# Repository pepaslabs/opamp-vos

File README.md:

# opamp-vos

A board to measure the Vos (input offset voltage) of op amps.

# Latest release: v2.1

* Gerbers: [gerbers.zip](kicad/releases/v2.1/gerbers.zip)
* Schematic: [pdf](kicad/releases/v2.1/opamp-vos.pdf).

# License

This board design is [Open-Source Hardware](http://www.oshwa.org/definition/).  It is licensed under the [MIT License](http://opensource.org/licenses/MIT).  It was designed by Jason Pepas.

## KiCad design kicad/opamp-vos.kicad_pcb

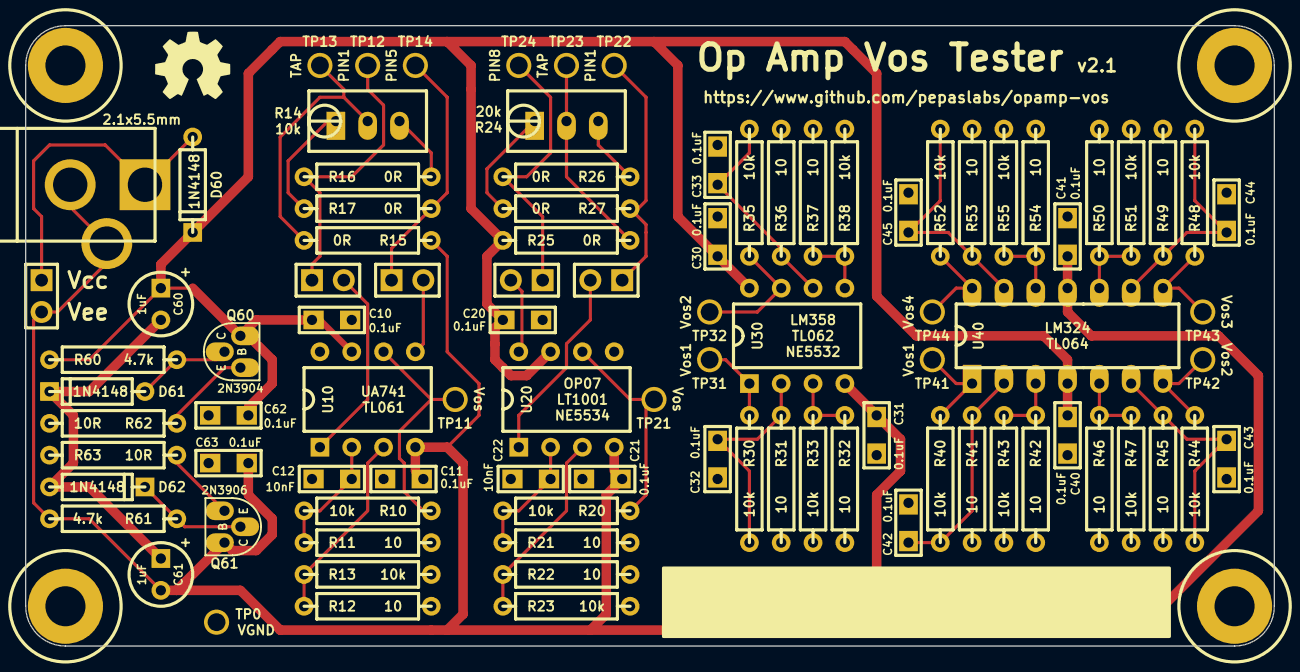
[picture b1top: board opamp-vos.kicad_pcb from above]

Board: 2 copper layers, 99.7 x 49.5 mm, 98 parts (0 on the bottom side), 47 nets.

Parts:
C10, C11, C20, C21, C30, C31, C32, C33, C40, C41, C42, C43, C44, C45, C62, C63: 0.1uF; CERCAP_15_059B_0805
C12, C22: 10nF; CERCAP_15_059B_0805
C60, C61: 1uF; ELCAP_10_20_V_059A
CON60: BARREL_JACK; BARREL_JACK_21x55
D60, D61, D62: 1N4148; DIODE_SS_059A_03_PL
H***: Val**; hole_M3
H***#2, H***#3, H***#4: Val**; hole_M3
JP10, JP11, JP20, JP21: JUMPER; SIL-2
P60: CONN_2X1; SIL-2
Q60: 2N3904; TO-92_Q_EBC_059Bo_PL
Q61: 2N3906; TO-92_Q_EBC_059Bo_PL
R10, R13, R20, R23, R30, R33, R35, R38, R40, R43, R44, R47, R48, R51, R52, R55: 10k; R_AXIAL_0W25_059A_PL
R11, R12, R21, R22, R31, R32, R36, R37, R41, R42, R45, R46, R49, R50, R53, R54: 10; R_AXIAL_0W25_059A_PL
R14: 10k; 3296W_PL
R15, R16, R17, R25, R26, R27: 0R; R_AXIAL_0W25_059A_PL
R24: 20k; 3296W_PL
R60, R61: 4.7k; R_AXIAL_0W25_059A_PL
R62, R63: 10R; R_AXIAL_0W25_059A_PL
TP0, TP11, TP12, TP13, TP14, TP21, TP22, TP23, TP24, TP31, TP32, TP41, TP42, TP43, TP44: TEST
U10: UA741; DIP8_059A_PL
U20: OP07; DIP8_059A_PL
U30: LM358; DIP8_059A_PL
U40: LM324; DIP14_PL

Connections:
unnamed: R42.1, R43.1, U40.3
unnamed: C42.1, R40.2, R41.1, U40.2
unnamed: C43.1, R44.2, R45.1, U40.6
unnamed: R46.1, R47.1, U40.5
unnamed: R24.2, R25.2, TP23.1
unnamed: JP21.1, R26.2, TP24.1
unnamed: R24.3, R26.1
unnamed: JP10.2, U10.1
unnamed: JP11.2, U10.5
unnamed: R14.3, R16.2
unnamed: JP20.2, U20.1
unnamed: JP21.2, U20.8
unnamed: R54.1, R55.1, U40.12
unnamed: R14.1, R17.1
unnamed: JP20.1, R27.1, TP22.1
unnamed: R24.1, R27.2
unnamed: C44.1, R48.2, R49.1, U40.9
unnamed: C45.1, R52.2, R53.1, U40.13
unnamed: R50.1, R51.1, U40.10
unnamed: CON60.1, D60.1, P60.1
unnamed: R32.1, R33.1, U30.3
unnamed: R12.1, R13.1, U10.3
unnamed: C12.1, R10.2, R11.1, U10.2
unnamed: D62.2, Q61.2, R61.1
unnamed: C60.2, C61.1, D61.2, D62.1
unnamed: D61.1, Q60.2, R60.2
unnamed: Q60.1, R62.1
unnamed: Q61.1, R63.2
unnamed: R14.2, R15.2, TP13.1
unnamed: JP10.1, R16.1, TP12.1
unnamed: JP11.1, R17.2, TP14.1
unnamed: C22.1, R20.2, R21.1, U20.2
unnamed: R22.1, R23.1, U20.3
unnamed: R37.1, R38.1, U30.5
unnamed: C32.1, R30.2, R31.1, U30.2
unnamed: C33.1, R35.2, R36.1, U30.6
Vcc: C10.1, C20.1, C30.1, C40.1, C60.1, C62.1, D60.2, Q60.3, R25.1, R60.1, U10.7, U20.7, U30.8, U40.4
Vee: C11.2, C21.2, C31.1, C41.1, C61.2, C63.2, CON60.2, CON60.3, P60.2, Q61.3, R15.1, R61.2, U10.4, U20.4, U30.4, U40.11
Vgnd: C10.2, C11.1, C12.2, C20.2, C21.1, C22.2, C30.2, C31.2, C32.2, C33.2, C40.2, C41.2, C42.2, C43.2, C44.2, C45.2, C62.2, C63.1, R11.2, R12.2, R13.2, R21.2, R22.2, R23.2, R31.2, R32.2, R33.2, R36.2, R37.2, R38.2, R41.2, R42.2, R43.2, R45.2, R46.2, R47.2, R49.2, R50.2, R51.2, R53.2, R54.2, R55.2, R62.2, R63.1, TP0.1
Vos1: R10.1, TP11.1, U10.6
Vos2: R20.1, TP21.1, U20.6
Vos3A: R30.1, TP31.1, U30.1
Vos3B: R35.1, TP32.1, U30.7
Vos4A: R40.1, TP41.1, U40.1
Vos4B: R44.1, TP42.1, U40.7
Vos4C: R48.1, TP43.1, U40.8
Vos4D: R52.1, TP44.1, U40.14

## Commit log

2017-04-22 Initial release
2017-04-22 adding board renders
2017-04-22 moving schematic
2017-05-19 Adding photo
2017-05-20 Rotating schematic
2018-06-09 working on revision 2
2018-06-09 schematic for v2
2018-06-10 working on v2 board layout
2018-06-10 v2 gerbers
2018-06-11 board shots, schematic
2018-06-21 v2.1
2018-06-23 board shots
2018-06-23 README
